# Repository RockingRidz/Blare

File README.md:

Blare
Blare is a coustom designed and planned alarm clock built by Me with the help of HackClub Nasa

What it does
Blare is a standalone alarm clock built with many components made to get you up in creativity. It has many switches and TFT diplay built into the 3D case.

Hardware and PCB 
I designed the PCB from scratch around an Seedx microcontroller module. The board includes:

Coustom copper wiring within the pcb.

Four push buttons for setting the time, toggling the alarm, and navigating menus.

A piezo buzzer for the alarm sound.

An TfT display connector.

Four mounting holes near the corners to attach the board securely inside the case.

Enclosure
The case was designed in Onshape to house the PCB, screen, and buttons 

Design: It uses a two-part split enclosure (a base and a lid) with M3 screw posts for assembly.

Openings: Cutouts on the front for the screen, side vents for airflow and buzzer sound, and a back slot for USB power.

Firmware
The firmware is written in C++ using the Arduino framework. It drives the Tft display, tracks time, listens for button presses to adjust the time/alarm, and triggers the buzzer when the alarm goes off.

Required Libraries:

Adafruit_GFX

Adafruit_ST7789

SPI

Current State
The PCB layout is finished, the Onshape case model is split and ready for printing, and the core alarm clock code is ready for testing on hardware.
images/PCB

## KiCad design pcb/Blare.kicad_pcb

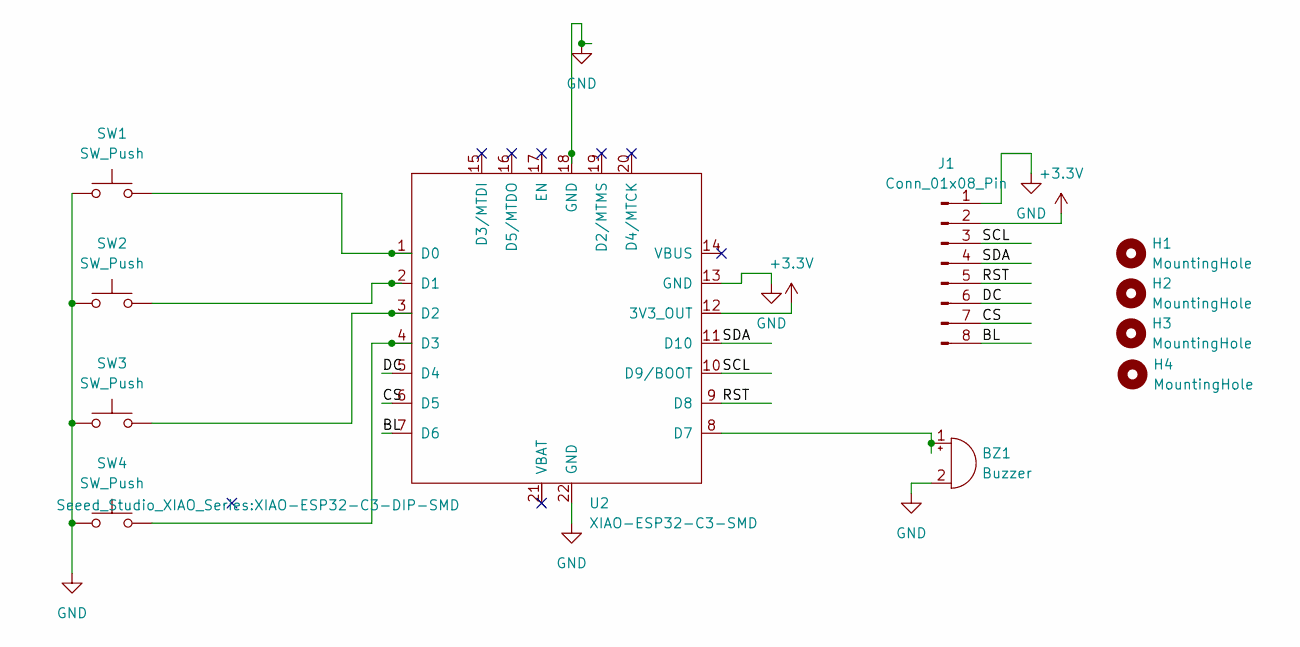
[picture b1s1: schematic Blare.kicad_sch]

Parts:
BZ1: Buzzer; Buzzer_12x9.5RM7.6
H1, H2, H3, H4: MountingHole; MountingHole_3.2mm_M3
J1: Conn_01x08_Pin; PinSocket_1x08_P2.54mm_Vertical
SW1, SW2, SW3, SW4: SW_Push; SW_Cherry_MX_1.00u_PCB
U2: XIAO-ESP32-C3-SMD; XIAO-ESP32-C3-DIP-SMD

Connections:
+3.3V: J1.2, U2.12 (3V3_OUT)
/BL: J1.8, U2.7 (D6)
/CS: J1.7, U2.6 (D5)
/DC: J1.6, U2.5 (D4)
/RST: J1.5, U2.9 (D8)
/SCL: J1.3, U2.10 (D9/BOOT)
/SDA: J1.4, U2.11 (D10)
GND: BZ1.2 (-), J1.1, SW1.1, SW2.1, SW3.1, SW4.1, U2.13 (GND), U2.18 (GND), U2.22 (GND)
unnamed: BZ1.1 (+), U2.8 (D7)
unnamed: SW1.2, U2.1 (D0)
unnamed: SW2.2, U2.2 (D1)
unnamed: SW3.2, U2.3 (D2)
unnamed: SW4.2, U2.4 (D3)

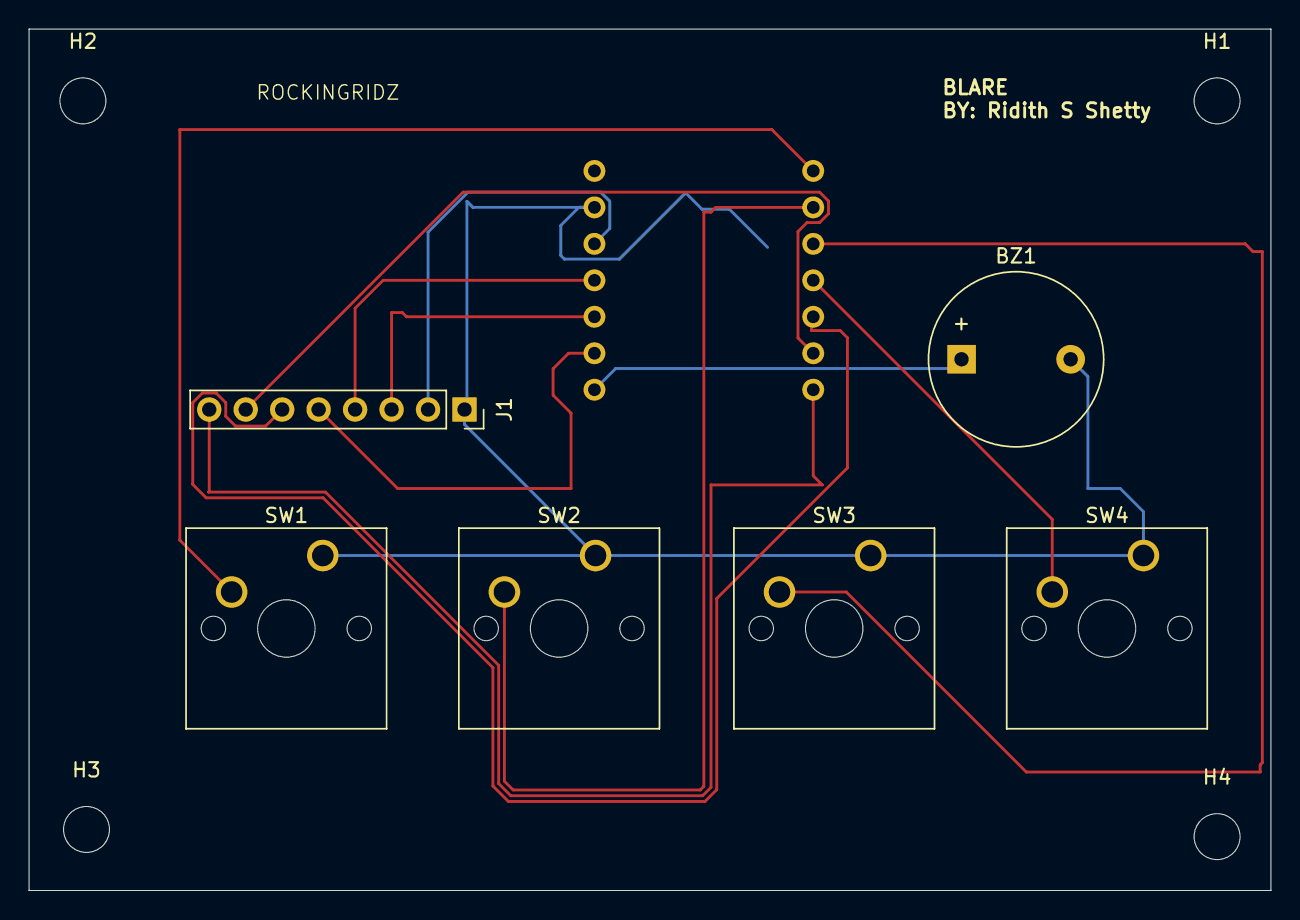
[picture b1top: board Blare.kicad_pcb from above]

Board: 2 copper layers, 86.5 x 60.0 mm, 11 parts (1 on the bottom side), 13 nets.
